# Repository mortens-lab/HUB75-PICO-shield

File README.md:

# HUB75-PICO-shield
HUB75 matrix display shield controlled by a Raspberry Pi Pico W

KiCad 7.0 files for shield

Link to youtube video : (https://youtu.be/hoFy992Y98c)

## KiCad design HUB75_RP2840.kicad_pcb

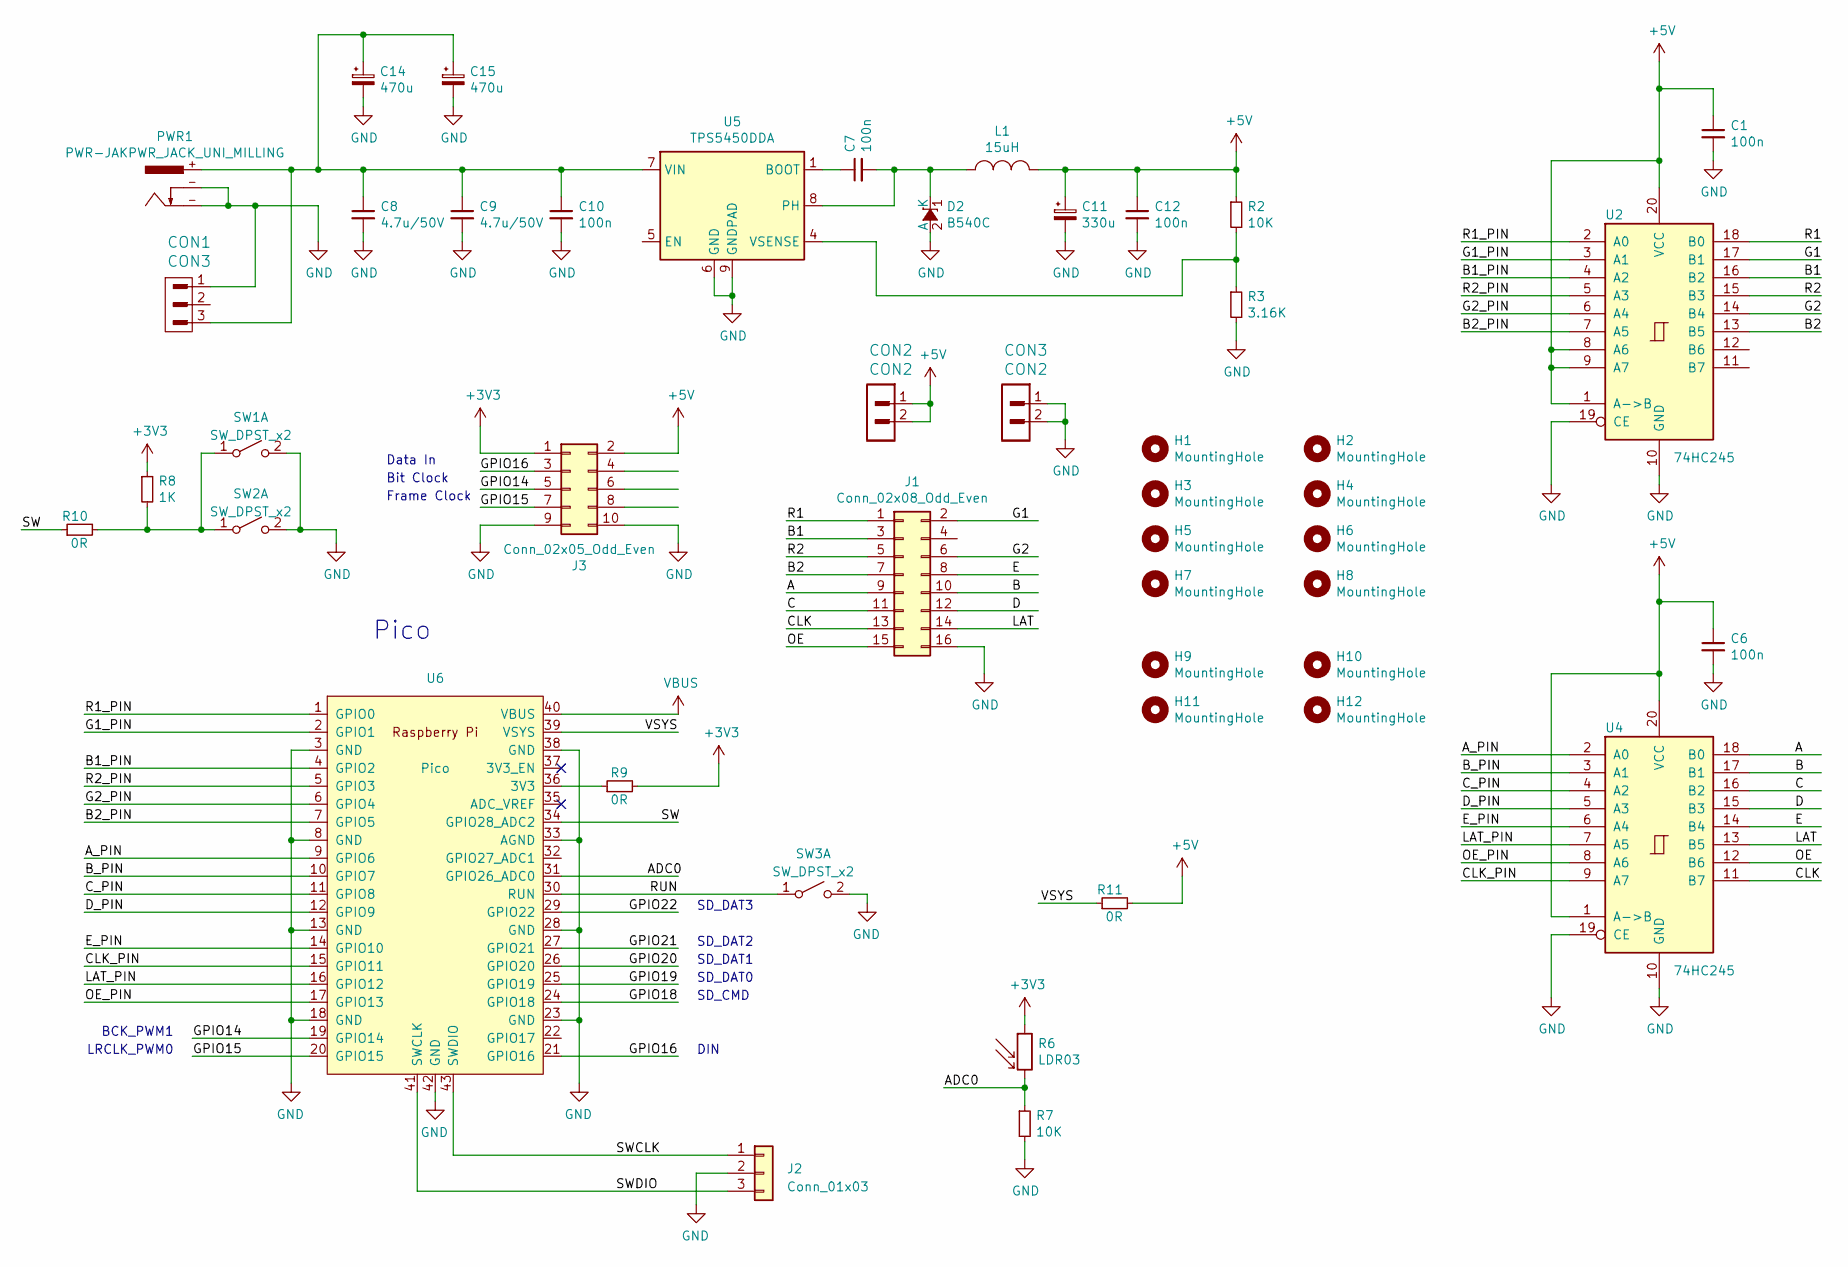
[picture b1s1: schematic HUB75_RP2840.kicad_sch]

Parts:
C1, C6, C7, C10, C12: 100n; C_0603_1608Metric
C8, C9: 4.7u/50V; C_1812_4532Metric
C11: 330u; CP_Elec_6.3x7.7
C14, C15: 470u; CP_Elec_8x10
CON1: CON3; TerminalBlock_Phoenix_MKDS-1,5-3-5.08_1x03_P5.08mm_Horizont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
CON2, CON3: CON2; TerminalBlock_Phoenix_MKDS-1,5-2-5.08_1x02_P5.08mm_Horizont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
D2: B540C; D_SMC
H1, H2, H3, H4, H5, H6, H7, H8: MountingHole; MountingHole_3.2mm_M3_Pad_Via
H9, H10, H11, H12: MountingHole; MountingHole_3.2mm_M3
J1: Conn_02x08_Odd_Even; IDC-Header_2x08_P2.54mm_Vertical
J2: Conn_01x03; PinHeader_1x03_P2.54mm_Vertical
J3: Conn_02x05_Odd_Even; PinHeader_2x05_P2.54mm_Vertical
L1: 15uH; L_12x12mm_H8mm
PWR1: PWR-JAKPWR_JACK_UNI_MILLING; PWRJ-2mm(YDJ-1136)
R2, R7: 10K; R_0603_1608Metric
R3: 3.16K; R_0603_1608Metric
R6: LDR03; R_LDR_10x8.5mm_P7.6mm_Vertical
R8: 1K; R_0603_1608Metric
R9, R10, R11: 0R; R_0603_1608Metric
SW1: SW_DPST_x2; SW_Tactile_SPST_Angled_PTS645Vx31-2LFS
SW2, SW3: SW_DPST_x2; SW_SPST_Omron_B3FS-100xP
U2, U4: 74HC245; SOIC-20W_7.5x12.8mm_P1.27mm
U5: TPS5450DDA; TI_SO-PowerPAD-8_ThermalVias
U6: Pico; RPi_Pico_WSMD_TH

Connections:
+3V3: J3.1, R6.1, R8.1, R9.2
+5V: C1.1, C6.1, C11.1, C12.1, CON2.1, CON2.2, J3.2, L1.2, R2.1, R11.2, U2.1 (A->B), U2.8 (A6), U2.9 (A7), U2.20 (VCC), U4.1 (A->B), U4.20 (VCC)
/A: J1.9, U4.18 (B0)
/ADC0: R6.2, R7.1, U6.31 (GPIO26_ADC0)
/A_PIN: U4.2 (A0), U6.9 (GPIO6)
/B: J1.10, U4.17 (B1)
/B1: J1.3, U2.16 (B2)
/B1_PIN: U2.4 (A2), U6.4 (GPIO2)
/B2: J1.7, U2.13 (B5)
/B2_PIN: U2.7 (A5), U6.7 (GPIO5)
/B_PIN: U4.3 (A1), U6.10 (GPIO7)
/C: J1.11, U4.16 (B2)
/CLK: J1.13, U4.11 (B7)
/CLK_PIN: U4.9 (A7), U6.15 (GPIO11)
/C_PIN: U4.4 (A2), U6.11 (GPIO8)
/D: J1.12, U4.15 (B3)
/D_PIN: U4.5 (A3), U6.12 (GPIO9)
/E: J1.8, U4.14 (B4)
/E_PIN: U4.6 (A4), U6.14 (GPIO10)
/G1: J1.2, U2.17 (B1)
/G1_PIN: U2.3 (A1), U6.2 (GPIO1)
/G2: J1.6, U2.14 (B4)
/G2_PIN: U2.6 (A4), U6.6 (GPIO4)
/GPIO14: J3.5, U6.19 (GPIO14)
/GPIO15: J3.7, U6.20 (GPIO15)
/GPIO16: J3.3, U6.21 (GPIO16)
/GPIO18: U6.24 (GPIO18)
/GPIO19: U6.25 (GPIO19)
/GPIO20: U6.26 (GPIO20)
/GPIO21: U6.27 (GPIO21)
/GPIO22: U6.29 (GPIO22)
/LAT: J1.14, U4.13 (B5)
/LAT_PIN: U4.7 (A5), U6.16 (GPIO12)
/OE: J1.15, U4.12 (B6)
/OE_PIN: U4.8 (A6), U6.17 (GPIO13)
/R1: J1.1, U2.18 (B0)
/R1_PIN: U2.2 (A0), U6.1 (GPIO0)
/R2: J1.5, U2.15 (B3)
/R2_PIN: U2.5 (A3), U6.5 (GPIO3)
/RUN: SW3.1 (A), U6.30 (RUN)
/SW: R10.1, U6.34 (GPIO28_ADC2)
/SWCLK: J2.1, U6.43 (SWDIO)
/SWDIO: J2.3, U6.41 (SWCLK)
/VSYS: R11.1, U6.39 (VSYS)
GND: C1.2, C6.2, C8.2, C9.2, C10.2, C11.2, C12.2, C14.2, C15.2, CON1.1, CON3.1, CON3.2, D2.2 (A), J1.16, J2.2, J3.9, J3.10, PWR1.-, R3.2, R7.2, SW1.2 (B), SW2.2 (B), SW3.2 (B), U2.10 (GND), U2.19 (CE), U4.10 (GND), U4.19 (CE), U5.6 (GND), U5.9 (GNDPAD), U6.3 (GND), U6.8 (GND), U6.13 (GND), U6.18 (GND), U6.23 (GND), U6.28 (GND), U6.33 (AGND), U6.38 (GND), U6.42 (GND)
unnamed: C7.2, D2.1 (K), L1.1, U5.8 (PH)
unnamed: R8.2, R10.2, SW1.1 (A), SW2.1 (A)
unnamed: C7.1, U5.1 (BOOT)
unnamed: C8.1, C9.1, C10.1, C14.1, C15.1, CON1.3, PWR1.+, U5.7 (VIN)
unnamed: R2.2, R3.1, U5.4 (VSENSE)
unnamed: R9.1, U6.36 (3V3)
VBUS: U6.40 (VBUS)

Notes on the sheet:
Pico
SD_DAT3
Bit Clock
SD_DAT2
SD_DAT0
SD_DAT1
Frame Clock
Data In
SD_CMD
LRCLK_PWM0
DIN
BCK_PWM1

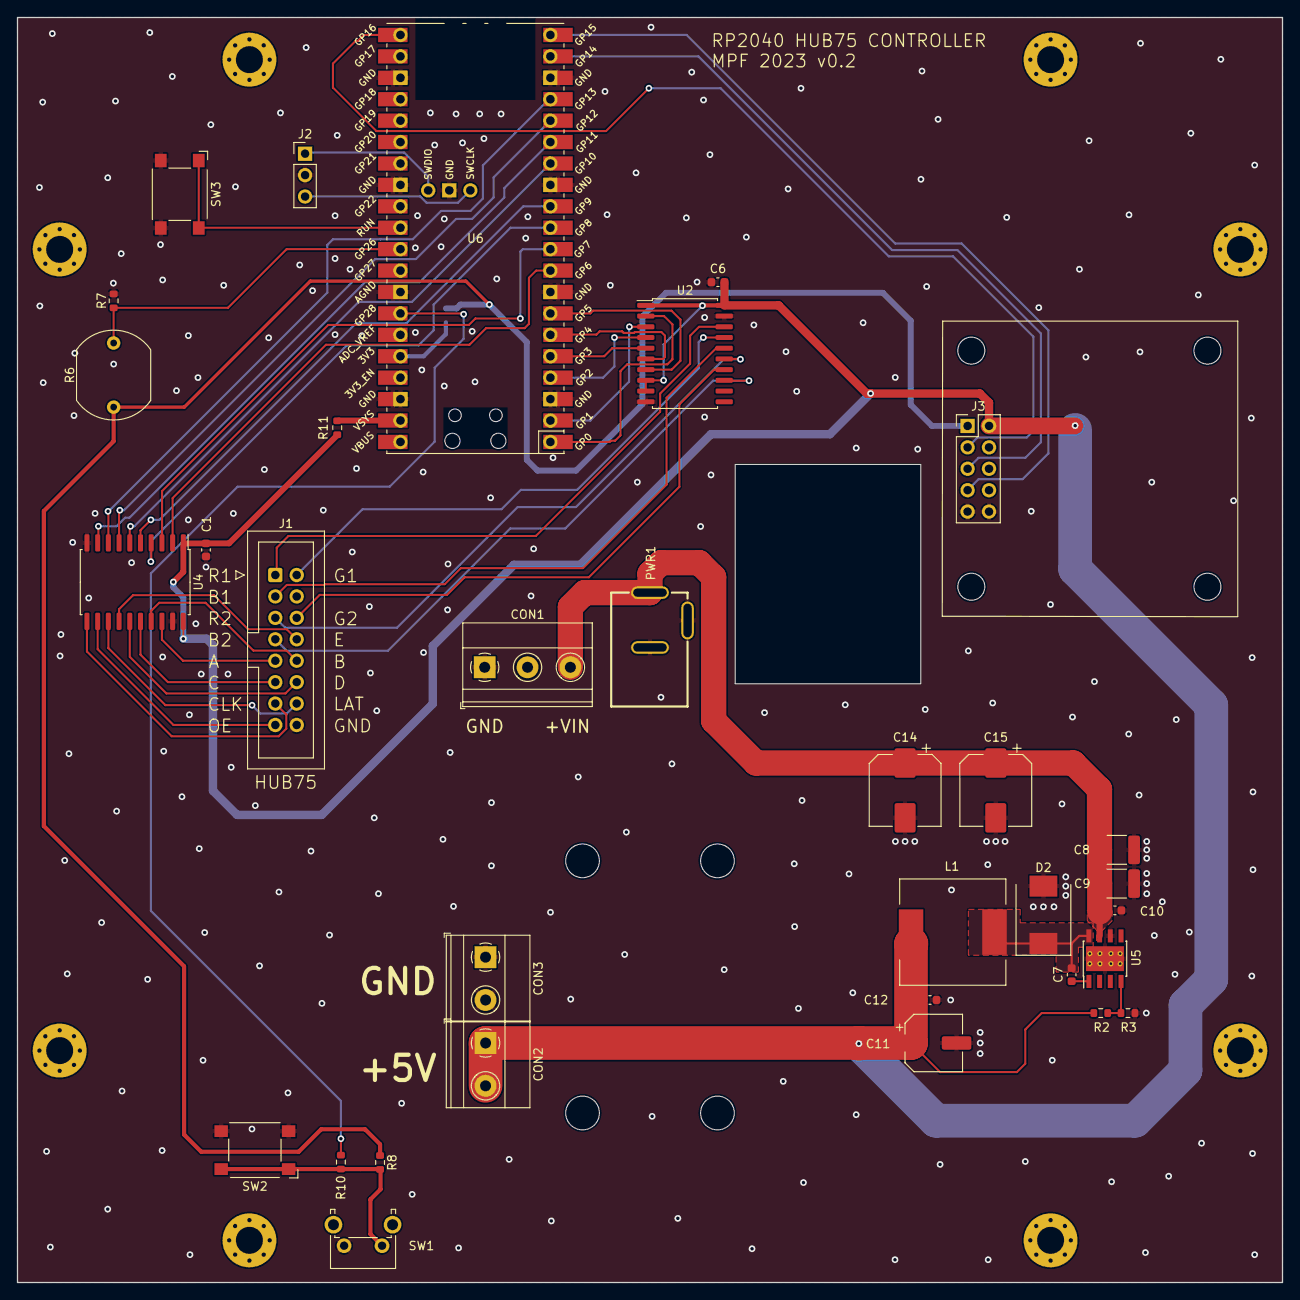
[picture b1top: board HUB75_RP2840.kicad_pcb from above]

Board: 2 copper layers, 150.0 x 150.0 mm, 46 parts (1 on the bottom side), 46 nets.

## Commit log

2024-02-27 Create code
